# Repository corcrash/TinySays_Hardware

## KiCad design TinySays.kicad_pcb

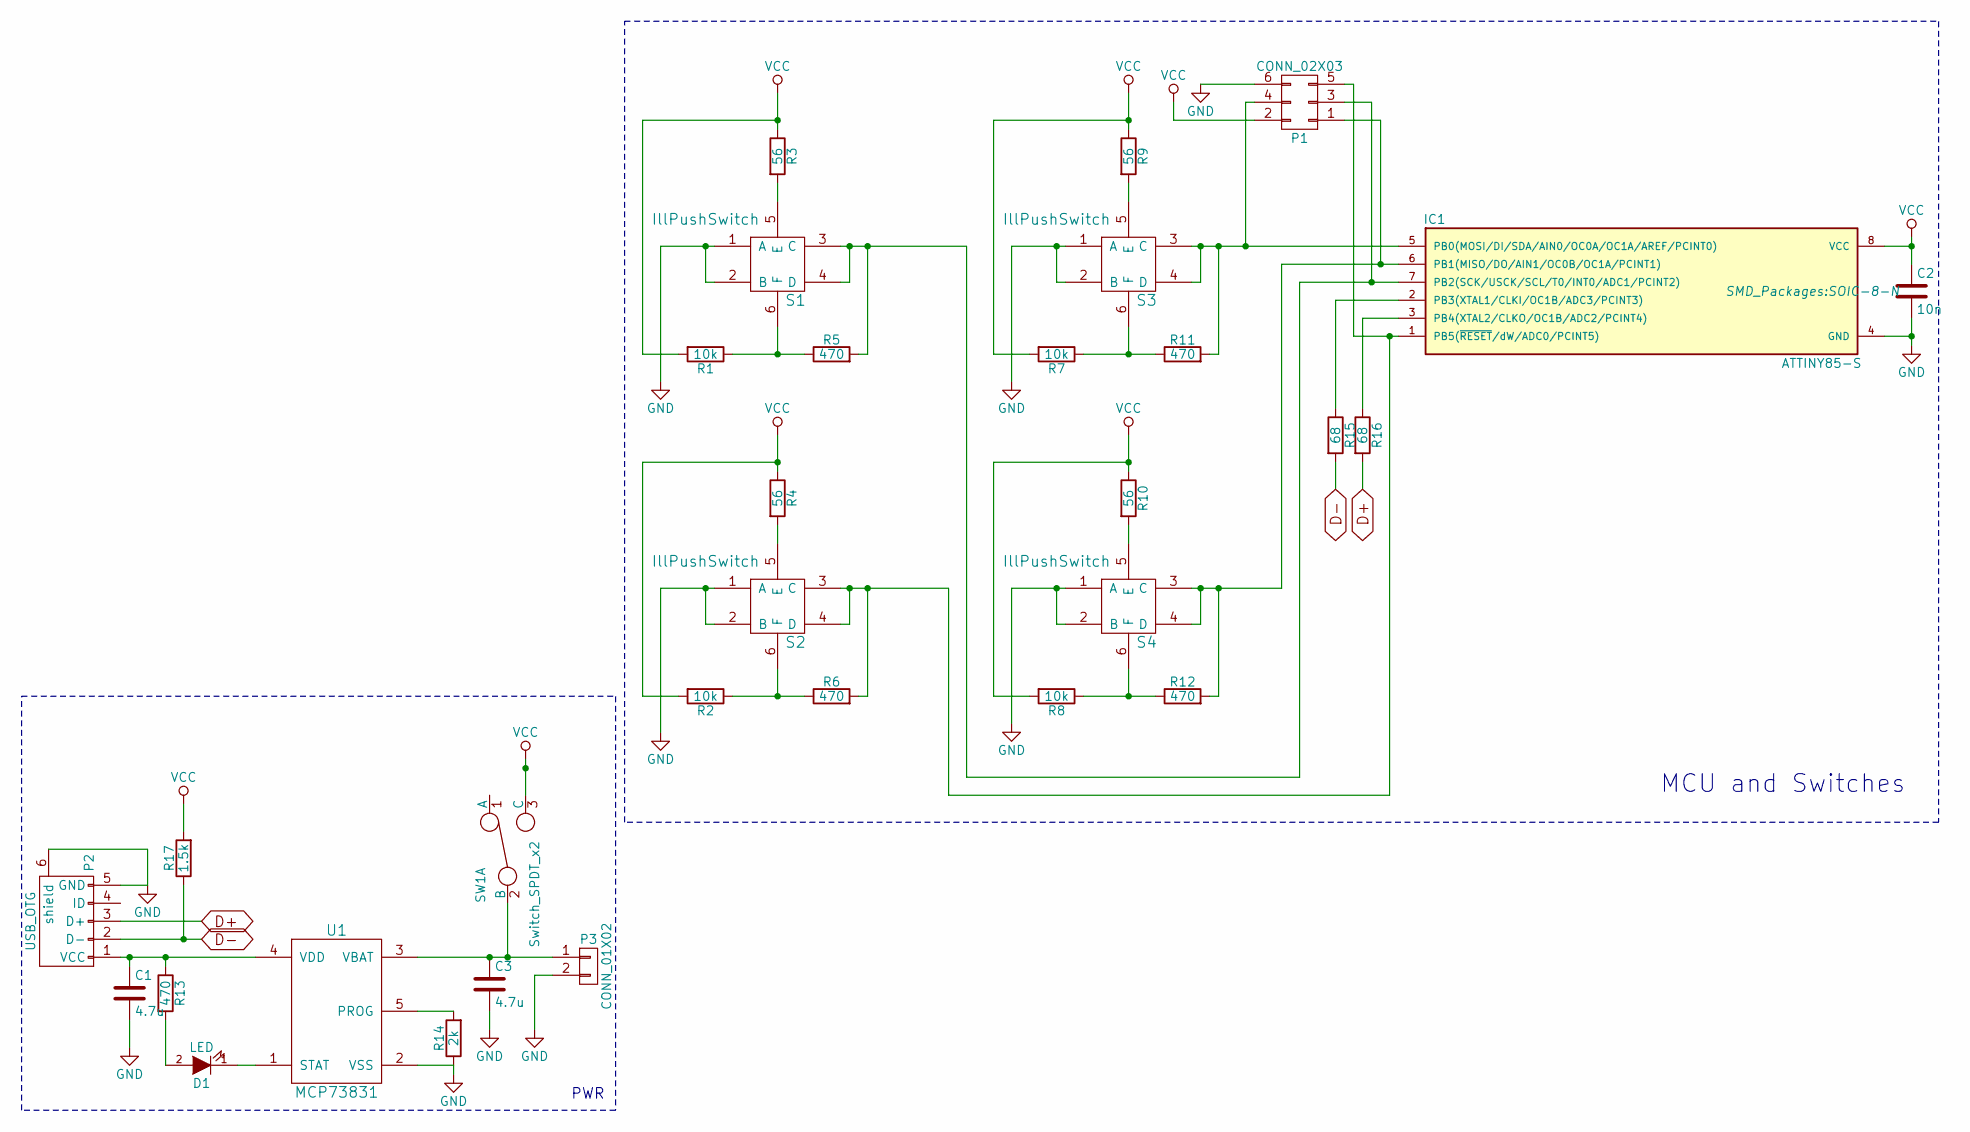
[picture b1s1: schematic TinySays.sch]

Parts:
C1, C3: 4.7u; C_0603_HandSoldering
C2: 10n; C_0603_HandSoldering
D1: LED; R_0603_HandSoldering
IC1: ATTINY85-S; SOIC-8-N
P1: CONN_02X03
P2: USB_OTG; USB_Micro-B
P3: CONN_01X02; Pin_Header_Angled_1x02
R1, R2, R7, R8: 10k; R_0603_HandSoldering
R3, R4, R9, R10: 56; R_0603_HandSoldering
R5, R6, R11, R12, R13: 470; R_0603_HandSoldering
R14: 2k; R_0603_HandSoldering
R15, R16: 68; R_0603_HandSoldering
R17: 1.5k; R_0603_HandSoldering
S1, S2, S3, S4: IllPushSwitch
SW1: Switch_SPDT_x2; STDP-2235S
U1: MCP73831; SOT-23-5

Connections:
D+: P2.3 (D+), R16.2
D-: P2.2 (D-), R15.2, R17.1
GND: C1.2, C2.2, C3.2, IC1.4 (GND), P1.6, P2.5 (GND), P2.6 (shield), P3.2, R14.1, S1.1 (A), S1.2 (B), S2.1 (A), S2.2 (B), S3.1 (A), S3.2 (B), S4.1 (A), S4.2 (B), U1.2 (VSS)
unnamed: C1.1, P2.1 (VCC), R13.1, U1.4 (VDD)
unnamed: C3.1, P3.1, SW1.2 (B), U1.3 (VBAT)
unnamed: D1.1 (K), U1.1 (STAT)
unnamed: D1.2 (A), R13.2
unnamed: IC1.1 (PB5(~RESET~/dW/ADC0/PCINT5)), P1.5, R6.2, S2.3 (C), S2.4 (D)
unnamed: IC1.2 (PB3(XTAL1/CLKI/OC1B/ADC3/PCINT3)), R15.1
unnamed: IC1.3 (PB4(XTAL2/CLKO/OC1B/ADC2/PCINT4)), R16.1
unnamed: IC1.5 (PB0(MOSI/DI/SDA/AIN0/OC0A/OC1A/AREF/PCI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), P1.4, R11.2, S3.3 (C), S3.4 (D)
unnamed: IC1.6 (PB1(MISO/DO/AIN1/OC0B/OC1A/PCINT1)), P1.1, R12.2, S4.3 (C), S4.4 (D)
unnamed: IC1.7 (PB2(SCK/USCK/SCL/T0/INT0/ADC1/PCINT2)), P1.3, R5.2, S1.3 (C), S1.4 (D)
unnamed: R1.1, R5.1, S1.6 (F)
unnamed: R2.1, R6.1, S2.6 (F)
unnamed: R3.2, S1.5 (E)
unnamed: R4.2, S2.5 (E)
unnamed: R9.2, S3.5 (E)
unnamed: R10.2, S4.5 (E)
unnamed: R7.1, R11.1, S3.6 (F)
unnamed: R8.1, R12.1, S4.6 (F)
unnamed: R14.2, U1.5 (PROG)
VCC: C2.1, IC1.8 (VCC), P1.2, R1.2, R2.2, R3.1, R4.1, R7.2, R8.2, R9.1, R10.1, R17.2, SW1.3 (C)

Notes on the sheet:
MCU and Switches
PWR

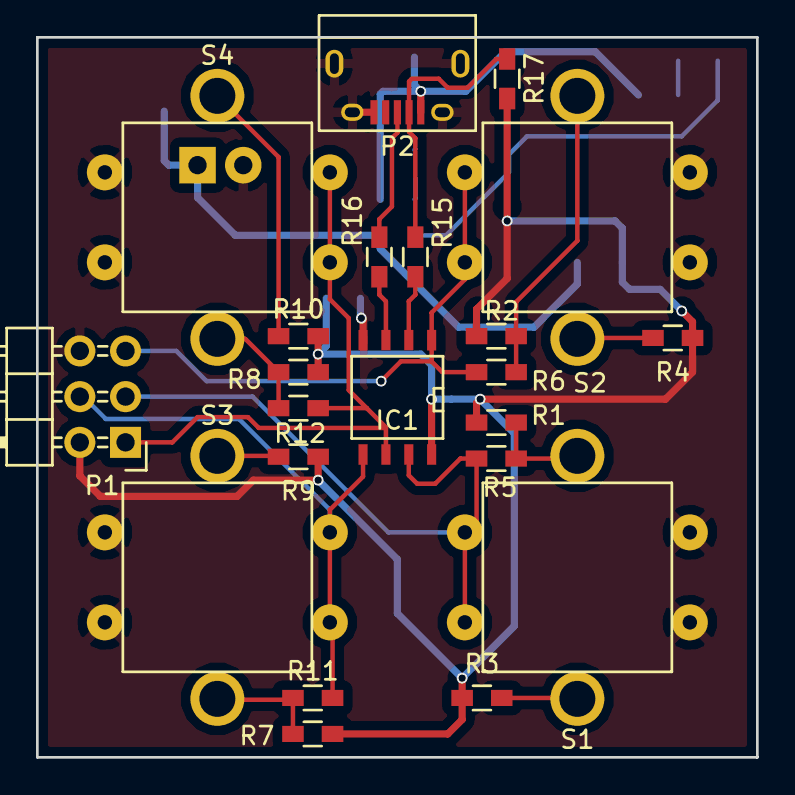
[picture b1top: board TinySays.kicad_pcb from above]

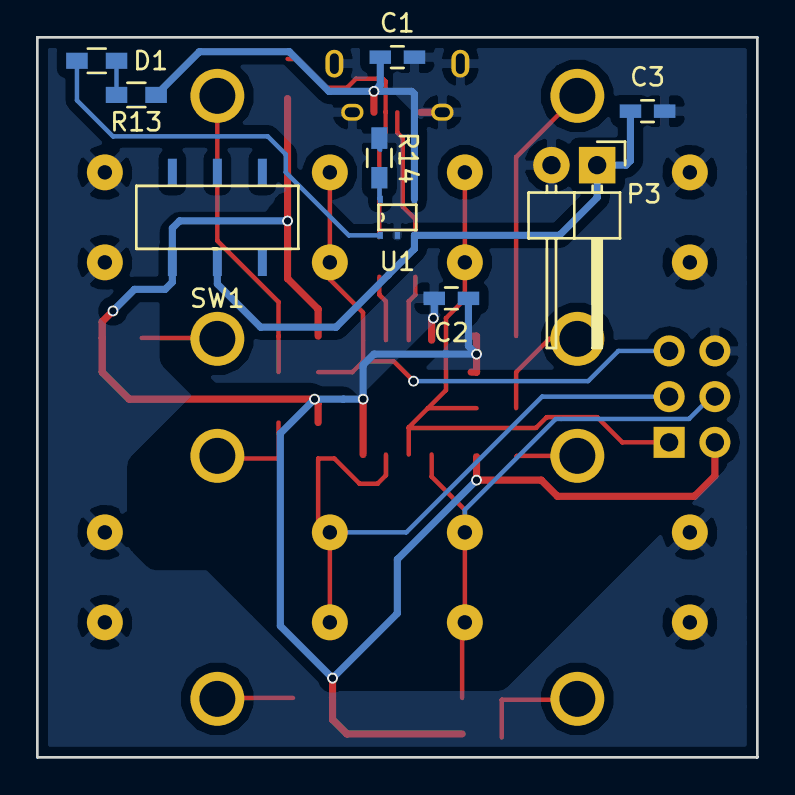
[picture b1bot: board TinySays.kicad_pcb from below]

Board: 2 copper layers, 40.0 x 40.0 mm, 31 parts (9 on the bottom side), 23 nets.

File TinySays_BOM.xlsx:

|  |  |  |  |  |  | Board Qty: | 5
 |  |  |  |  |  |  | Total Cost: | 2576.2 |  |  |  | 0 |  |  |  |  |  | 0 |  |  |  |  |  | 0
 |  |  |  |  |  |  | Unit Cost: | 515.24
Global Part Info |  |  |  |  |  |  |  |  | Digi-Key |  |  |  |  |  | Mouser |  |  |  |  |  | Newark
Refs | Value | Desc | Footprint | Manf | Manf# | Qty | Unit$ | Ext$ | Avail | Purch | Unit$ | Ext$ | Cat# | Doc | Avail | Purch | Unit$ | Ext$ | Cat# | Doc | Avail | Purch | Unit$ | Ext$ | Cat# | Doc
R3,R4,R9,R10 | 56 |  | Resistors_SMD:R_0603_HandSoldering |  |  | 20 | 0.5 | 10
R1,R2,R7,R8 | 10k |  | Resistors_SMD:R_0603_HandSoldering |  |  | 20 | 0.5 | 10
IC1 | ATTINY85-S |  | SMD_Packages:SOIC-8-N |  |  | 5 | 93.31 | 466.55
S1-S4 | IllPushSwitch |  | TinySays:IllPushSwitch |  |  | 20 | 35.8 | 716
C1,C3 | 4.7u |  | Capacitors_SMD:C_0603_HandSoldering |  |  | 10 | 1.908 | 19.08
U1 | MCP73831 |  | TinySays:SOT-23-5 |  |  | 5 | 70.44 | 352.2
C2 | 10n |  | Capacitors_SMD:C_0603_HandSoldering |  |  | 5 | 0.984 | 4.92
R5,R6,R11-R13 | 470 |  | Resistors_SMD:R_0603_HandSoldering |  |  | 25 | 0.5 | 12.5
P2 | USB_OTG |  | Connect:USB_Micro-B |  |  | 5 | 72.41 | 362.05
SW1 | Switch_SPDT_x2 |  | TinySays:STDP-2235S |  |  | 5 | 109.99 | 549.95
D1 | LED |  | Resistors_SMD:R_0603_HandSoldering |  |  | 5 | 8 | 40
R17 | 1.5k |  | Resistors_SMD:R_0603_HandSoldering |  |  | 5 | 0.5 | 2.5
R14 | 2k |  | Resistors_SMD:R_0603_HandSoldering |  |  | 5 | 2.89 | 14.45
R15,R16 | 68 |  | Resistors_SMD:R_0603_HandSoldering |  |  | 10 | 0.5 | 5
P3 | CONN_01X02 |  | Pin_Headers:Pin_Header_Angled_1x02 |  |  | 5 | 2.2 | 11

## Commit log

2016-04-20 PCB v2.0 40mm x 40mm done
2016-04-20 Changed the position of the battery connector.
2016-04-21 Cleaned up the routing a bit.
